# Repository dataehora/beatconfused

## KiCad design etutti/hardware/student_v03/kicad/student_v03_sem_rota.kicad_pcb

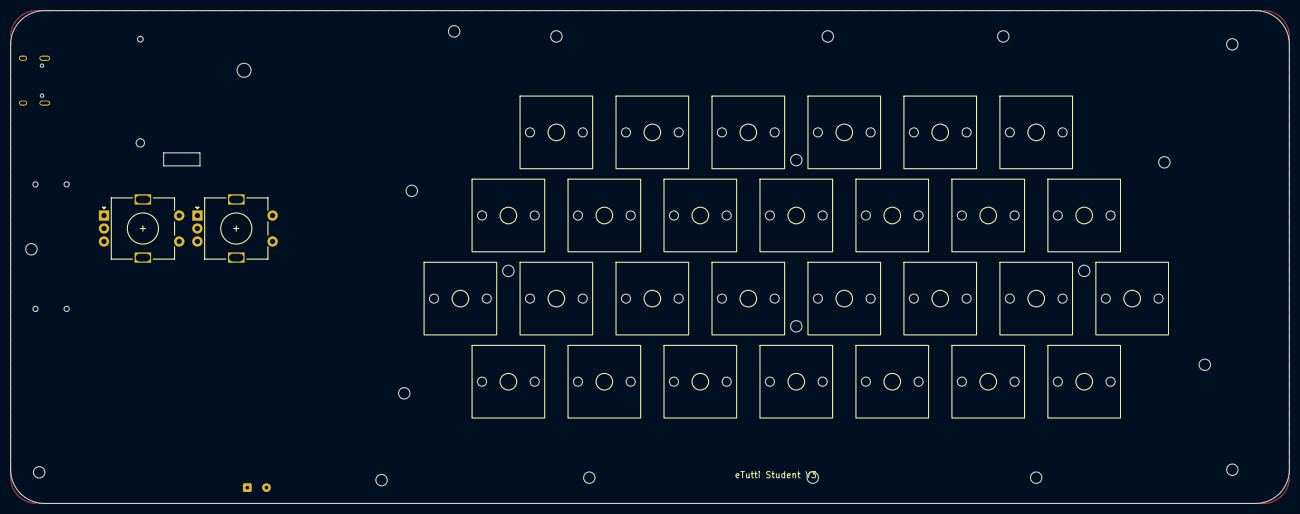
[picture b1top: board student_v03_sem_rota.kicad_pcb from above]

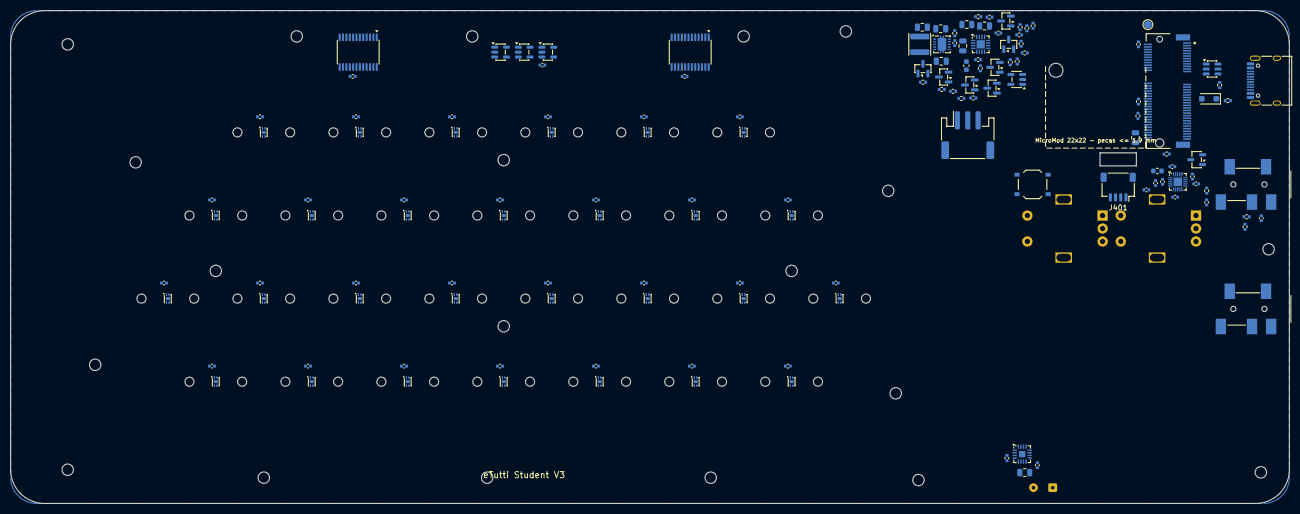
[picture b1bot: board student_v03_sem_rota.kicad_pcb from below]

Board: 4 copper layers, 246.5 x 95.0 mm, 190 parts (138 on the bottom side), 98 nets, no tracks yet.

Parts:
C101, C201, C202, C203, C206, C207, C208, C501: 10uF; C_0805_2012Metric
C102, C204, C205, C209, C302, C304, C305, C307, C308, C502, C601, C602, C603, C701, C702, C703, C704, C705, C706, C707, C708, C709, C710, C711, C712, C713, C714, C715, C716, C717, C718, C719, C720, C721, C722, C723, C724, C725, C726, C727, C728: 100nF; C_0402_1005Metric
C210: 10uF; C_0603_1608Metric
C213, C309: 1uF; C_0402_1005Metric
C301, C303, C306: 2.2uF; C_0402_1005Metric
D201: SMF5.0A; D_SOD-123F
D202, D203, D204, D205: BAV70; SOT-23
FB301: 600R@100MHz; L_0603_1608Metric
H1, H2, H3, H4, H5, H6, H7, H8, H9, H10: MountingHole_2.2mm_M2
H101: MountingHole_2.7mm_M2.5
HG1, HG2, HG3, HG4, HG5, HG6, HG7, HG8, HG9, HG10: MountingHole_2.2mm_M2
J101: 91302-42-067RCE; M.2_E_H4.2_UMAX_91302-42-067
J201: TYPE-C-31-M-12; USB_C_Receptacle_HRO_TYPE-C-31-M-12
J202: S3B-PH-SM4-TB; JST_PH_S3B-PH-SM4-TB_1x03-1MP_P2.00mm_Horizontal
J301, J302: PJ-327A 5JJ; Jack_3.5mm_PJ-327A_SMD
J401: SM04B-SRSS-TB; JST_SH_SM04B-SRSS-TB_1x04-1MP_P1.00mm_Horizontal
J501: alto-falante (fios); SolderWire-0.127sqmm_1x02_P3.7mm_D0.48mm_OD1mm
L201: 2.2uH; L_Changjiang_FNR4020S
Q201, Q203: AO3401A; SOT-23
Q202: AO3400A; SOT-23
R105, R216: 100; R_0402_1005Metric
R201, R202: 5.1k; R_0402_1005Metric
R203, R301, R302, R305: 2.2k; R_0402_1005Metric
R204: 1.5k; R_0402_1005Metric
R205, R214: 10k; R_0402_1005Metric
R206, R210, R211, R213, R215, R218, R303: 100k; R_0402_1005Metric
R207, R217: 1k; R_0402_1005Metric
R208, R209, R212, R304, R501: 1M; R_0402_1005Metric
SW1, SW2, SW3, SW4, SW5, SW6, SW7, SW8, SW9, SW10, SW11, SW12, SW13, SW14, SW15, SW16, SW17, SW18, SW19, SW20, SW21, SW22, SW23, SW24, SW25, SW26, SW27, SW28: Gateron_Magnetic_MX_1u
SW401, SW402: EC11E18244AU; RotaryEncoder_Alps_EC11E-Switch_Vertical_H20mm
SW403: Program; SW_Push_1P1T_XKB_TS-1187A
TP101: RESET#/ONOFF; TestPoint_Pad_D1.5mm
U201: USBLC6-2SC6; SOT-23-6
U202: BQ24074RGTR; VQFN-16-1EP_3x3mm_P0.5mm_EP1.6x1.6mm
U203, U604, U605: 74LVC1G08; SOT-23-5
U204: TPS63001DRCR; Texas_DRC0010J
U301: SGTL5000XNLA3; QFN-20-1EP_3x3mm_P0.4mm_EP1.65x1.65mm
U302: XC6206P182MR; SOT-23-3
U501: MAX98357AETE+T; TQFN-16-1EP_3x3mm_P0.5mm_EP1.23x1.23mm
U601, U602: 74HC4067PW; TSSOP-24_4.4x7.8mm_P0.65mm
U603: 74LVC1G04; SOT-23-5
U701, U702, U703, U704, U705, U706, U707, U708, U709, U710, U711, U712, U713, U714, U715, U716, U717, U718, U719, U720, U721, U722, U723, U724, U725, U726, U727, U728: TMAG5253BA3IQDMRR; Texas_X2SON-4-1EP_1.1x1.4mm_P0.5mm_EP0.8x0.6mm

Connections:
+3V3: C101.1, C102.1, C205.1, C207.1, C208.1, C303.1, C304.1, C305.1, C601.1, C602.1, C603.1, C701.1, C702.1, C703.1, C704.1, C705.1, C706.1, C707.1, C708.1, C709.1, C710.1, C711.1, C712.1, C713.1, C714.1, C715.1, C716.1, C717.1, C718.1, C719.1, C720.1, C721.1, C722.1, C723.1, C724.1, C725.1, C726.1, C727.1, C728.1, FB301.1, J101.2, J101.74, J401.2, Q202.1, R218.1, R301.1, R302.1, U203.5, U204.1, U204.10, U301.12, U302.3, U601.24, U602.24, U603.5, U604.5, U605.5, U701.1, U702.1, U703.1, U704.1, U705.1, U706.1, U707.1, U708.1, U709.1, U710.1, U711.1, U712.1, U713.1, U714.1, U715.1, U716.1, U717.1, U718.1, U719.1, U720.1, U721.1, U722.1, U723.1, U724.1, U725.1, U726.1, U727.1, U728.1
AMP_SD: J101.61, R501.1
AMP_SDM: R501.2, U501.4
AUD_MCLK: R105.2, U301.13
AUD_MCLK_P: J101.58, R105.1
BAT_NTC: J202.2, U202.1
BB_L1: L201.1, U204.4
BB_L2: L201.2, U204.2
BB_VINA: C209.1, R216.2, U204.8
CC1: J201.A5, R201.1
CC2: J201.B5, R202.1
CHGA: Q202.3, R207.2
CHGLED: Q201.3, R207.1
CHG_EN1: R205.2, U202.6
CHG_ILIM: R204.1, U202.12
CHG_ISET: R203.1, U202.16
CHG_N: D202.3, Q201.1, R206.2, U202.9
CHG_STAT: D202.1, J101.67
EN_A: U604.4, U701.3, U702.3, U703.3, U704.3, U705.3, U706.3, U707.3, U716.3, U717.3, U718.3, U719.3, U720.3, U721.3, U722.3
EN_B: U605.4, U708.3, U709.3, U710.3, U711.3, U712.3, U713.3, U714.3, U715.3, U723.3, U724.3, U725.3, U726.3, U727.3, U728.3
EN_REQ: D203.3, D204.3, R212.1, U204.6
GND: C101.2, C102.2, C201.2, C202.2, C203.2, C204.2, C205.2, C206.2, C207.2, C208.2, C209.2, C210.2, C213.2, C301.2, C302.2, C303.2, C304.2, C305.2, C306.2, C307.2, C308.2, C501.2, C502.2, C601.2, C602.2, C603.2, C701.2, C702.2, C703.2, C704.2, C705.2, C706.2, C707.2, C708.2, C709.2, C710.2, C711.2, C712.2, C713.2, C714.2, C715.2, C716.2, C717.2, C718.2, C719.2, C720.2, C721.2, C722.2, C723.2, C724.2, C725.2, C726.2, C727.2, C728.2, D201.2, J101.1, J101.7, J101.33, J101.36, J101.39, J101.45, J101.75, J101.MP, J201.A1, J201.A12, J201.B1, J201.B12, J201.SH, J202.3, J202.MP, J302.1, J302.2, J401.1, J401.MP, Q202.2, R201.2, R202.2, R203.2, R204.2, R209.2, R211.2, R212.2, R213.2, R215.2, R304.2, SW401.C, SW401.MP, SW401.S1, SW402.C, SW402.MP, SW402.S1, SW403.2, U201.2, U202.4, U202.5, U202.8, U202.17, U203.3, U204.3, U204.7, U204.9, U204.11, U301.21, U302.1, U501.3, U501.11, U501.15, U501.17, U601.12, U601.15, U602.12, U602.15, U603.3, U604.3, U605.3, U701.2, U701.5, U702.2, U702.5, U703.2, U703.5, U704.2, U704.5, U705.2, U705.5, U706.2, U706.5, U707.2, U707.5, U708.2, U708.5, U709.2, U709.5, U710.2, U710.5, U711.2, U711.5, U712.2, U712.5, U713.2, U713.5, U714.2, U714.5, U715.2, U715.5, U716.2, U716.5, U717.2, U717.5, U718.2, U718.5, U719.2, U719.5, U720.2, U720.5, U721.2, U721.5, U722.2, U722.5, U723.2, U723.5, U724.2, U724.5, U725.2, U725.5, U726.2, U726.5, U727.2, U727.5, U728.2, U728.5
HP_DET: C308.1, J101.22, R303.2, R304.1
HP_L: J301.4, U301.4
HP_R: J301.3, U301.1
HP_TIPSW: J301.5, R303.1
HP_VGND: J301.1, J301.2, U301.2
I2C_SCL: J101.14, J401.4, R302.2, U301.19
I2C_SDA: J101.12, J401.3, R301.2, U301.18
I2S_BCLK: J101.50, U301.15, U501.16
I2S_LRCLK: J101.52, U301.14, U501.14
I2S_RX: J101.54, U301.16
I2S_TX: J101.56, U301.17, U501.1
KEEP: D203.2, J101.55, R213.1
MIC_BIAS: R305.1, U301.11
MIC_IN: C309.2, U301.10
MIC_J: C309.1, J302.4, R305.2
MUX_L_COM: J101.38, U601.1
MUX_R_COM: J101.34, U602.1
MUX_S0: J101.19, U601.10, U602.10
MUX_S1: J101.17, U601.11, U602.11
MUX_S2: J101.47, U601.14, U602.14
MUX_S3: J101.32, U601.13, U602.13, U603.2, U605.1
NS3: U603.4, U604.1
ONOFF: D205.2, J101.6, TP101.1
OUT_K01: U601.4, U701.4
OUT_K02: U601.5, U702.4
OUT_K03: U601.8, U703.4
OUT_K04: U601.6, U704.4
OUT_K05: U602.7, U705.4
OUT_K06: U602.8, U706.4
OUT_K07: U602.9, U707.4
OUT_K08: U601.22, U708.4
OUT_K09: U601.21, U709.4
OUT_K10: U601.16, U710.4
OUT_K11: U601.18, U711.4
OUT_K12: U602.18, U712.4
OUT_K13: U602.20, U713.4
OUT_K14: U602.17, U714.4
OUT_K15: U602.16, U715.4
OUT_K16: U601.7, U716.4
OUT_K17: U601.2, U717.4
OUT_K18: U601.3, U718.4
OUT_K19: U602.5, U719.4
OUT_K20: U602.3, U720.4
OUT_K21: U602.4, U721.4
OUT_K22: U602.6, U722.4
OUT_K23: U601.19, U723.4
OUT_K24: U601.20, U724.4
OUT_K25: U601.23, U725.4
OUT_K26: U602.22, U726.4
OUT_K27: U602.23, U727.4
OUT_K28: U602.21, U728.4
PROG: J101.11, SW403.1
PWR_EN: J101.4, R217.1
PWR_EN_S: C213.1, R217.2, R218.2, U203.2
PWR_KEY: D203.1, Q203.3, R211.1
SEL_A: J101.59, SW402.A
SEL_B: J101.69, SW402.B
SEL_SW: J101.71, SW402.S2
SENS_EN: J101.10, U604.2, U605.2
SGTL_VAG: C307.1, U301.5
SGTL_VDDA: C301.1, C302.1, FB301.2, U301.3
SGTL_VDDD: C306.1, U301.20, U302.2
SPK_N: J501.2, U501.10
SPK_P: J501.1, U501.9
USB_DN: J101.5, J201.A7, J201.B7, U201.3, U201.4
USB_DP: J101.3, J201.A6, J201.B6, U201.1, U201.6
USB_HOLD: D204.1, U203.4
VBAT: C203.1, J202.1, R208.1, U202.2, U202.3
VBAT_S: C204.1, J101.20, R208.2, R209.1
VBUS: C201.1, D201.1, J101.9, J201.A4, J201.A9, J201.B4, J201.B9, Q201.2, R205.1, R206.1, R214.1, U201.5, U202.13
VBUS_S: R214.2, R215.1, U203.1
VOL_A: J101.49, SW401.A
VOL_B: J101.53, SW401.B
VOL_SW: D205.1, J101.51
VOL_SW_N: D205.3, Q203.1, R210.2, SW401.S2
VSYS: C202.1, C206.1, C210.1, C501.1, C502.1, Q203.2, R210.1, R216.1, U202.10, U202.11, U204.5, U501.7, U501.8

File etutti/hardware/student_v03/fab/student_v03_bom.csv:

Comment,Designator,Footprint,LCSC Part #
100nF,"C102,C204,C205,C209,C302,C304,C305,C307,C308,C502,C601,C602,C603,C701,C702,C703,C704,C705,C706,C707,C708,C709,C710,C711,C712,C713,C714,C715,C716,C717,C718,C719,C720,C721,C722,C723,C724,C725,C726,C727,C728",C_0402_1005Metric,C1525
2.2uF,"C301,C303,C306",C_0402_1005Metric,C12530
1uF,C309,C_0402_1005Metric,C52923
10uF,C210,C_0603_1608Metric,C19702
10uF,"C101,C201,C202,C203,C206,C207,C208,C501",C_0805_2012Metric,C15850
SMF5.0A,D201,D_SOD-123F,C151296
S3B-PH-SM4-TB,J202,JST_PH_S3B-PH-SM4-TB_1x03-1MP_P2.00mm_Horizontal,C265101
SM04B-SRSS-TB,J401,JST_SH_SM04B-SRSS-TB_1x04-1MP_P1.00mm_Horizontal,C160404
PJ-327A,"J301,J302",Jack_3.5mm_PJ-327A_SMD,C49284723
600R@100MHz,FB301,L_0603_1608Metric,C1002
2.2uH,L201,L_Changjiang_FNR4020S,C167825
91302-42-067RCE,J101,M.2_E_H4.2_UMAX_91302-42-067,C48985906
SGTL5000XNLA3,U301,QFN-20-1EP_3x3mm_P0.4mm_EP1.65x1.65mm,C2651833
100,"R105,R216",R_0402_1005Metric,C25076
5.1k,"R201,R202",R_0402_1005Metric,C25905
2.2k,"R203,R301,R302,R305",R_0402_1005Metric,C25879
1.5k,R204,R_0402_1005Metric,C25867
10k,"R205,R214",R_0402_1005Metric,C25744
100k,"R206,R210,R211,R213,R215,R303",R_0402_1005Metric,C25741
1M,"R208,R209,R212,R304,R501",R_0402_1005Metric,C26083
BAV70,"D202,D203,D205,D206",SOT-23,C68978
AO3401A,Q203,SOT-23,C15127
XC6206P182MR,U302,SOT-23-3,C347373
74LVC1G04,U603,SOT-23-5,C7827
74LVC1G08,"U604,U605",SOT-23-5,C7666
USBLC6-2SC6,U201,SOT-23-6,C7519
Program,SW403,SW_Push_1P1T_XKB_TS-1187A,C318884
MAX98357AETE+T,U501,TQFN-16-1EP_3x3mm_P0.5mm_EP1.23x1.23mm,C910544
74HC4067PW,"U601,U602",TSSOP-24_4.4x7.8mm_P0.65mm,C179326
TPS63001DRCR,U204,Texas_DRC0010J,C28060
TMAG5253BA3IQDMRR,"U701,U702,U703,U704,U705,U706,U707,U708,U709,U710,U711,U712,U713,U714,U715,U716,U717,U718,U719,U720,U721,U722,U723,U724,U725,U726,U727,U728",Texas_X2SON-4-1EP_1.1x1.4mm_P0.5mm_EP0.8x0.6mm,C22401868
TYPE-C-31-M-12,J201,USB_C_Receptacle_HRO_TYPE-C-31-M-12,C165948
BQ24074RGTR,U202,VQFN-16-1EP_3x3mm_P0.5mm_EP1.6x1.6mm,C54313

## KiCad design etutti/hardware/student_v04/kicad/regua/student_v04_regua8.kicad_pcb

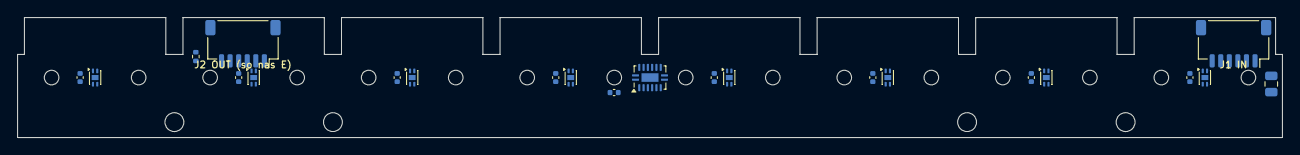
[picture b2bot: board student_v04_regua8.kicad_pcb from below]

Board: 4 copper layers, 147.6 x 14.0 mm, 42 parts (22 on the bottom side), 15 nets, no tracks yet.

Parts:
C1, C2, C3, C4, C5, C6, C7, C8, C9: 100nF; C_0402_1005Metric
C10: 10uF; C_0805_2012Metric
H1, H2, H3, H4: MountingHole_2.2mm_M2
J1, J2: SM06B-SRSS-TB(LF)(SN); JST_SH_SM06B-SRSS-TB_1x06-1MP_P1.00mm_Horizontal
PEG1a, PEG1b, PEG2a, PEG2b, PEG3a, PEG3b, PEG4a, PEG4b, PEG5a, PEG5b, PEG6a, PEG6b, PEG7a, PEG7b, PEG8a, PEG8b: MountingHole_2.2mm_M2
R1: 330; R_0402_1005Metric
U1, U2, U3, U4, U5, U6, U7, U8: TMAG5253BA3IQDMRR; Texas_X2SON-4-1EP_1.1x1.4mm_P0.5mm_EP0.8x0.6mm
U9: 74HC595BQ,115; DHVQFN-16-1EP_2.5x3.5mm_P0.5mm_EP1x2mm

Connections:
+3V3: C1.1, C2.1, C3.1, C4.1, C5.1, C6.1, C7.1, C8.1, C9.1, C10.1, J1.1, J2.1, U1.1, U2.1, U3.1, U4.1, U5.1, U6.1, U7.1, U8.1, U9.10, U9.16
CLK: J1.5, J2.5, U9.11, U9.12
EN1: U1.3, U9.15
EN2: U2.3, U9.1
EN3: U3.3, U9.2
EN4: U4.3, U9.3
EN5: U5.3, U9.4
EN6: U6.3, U9.5
EN7: U7.3, U9.6
EN8: U8.3, U9.7
GND: C1.2, C2.2, C3.2, C4.2, C5.2, C6.2, C7.2, C8.2, C9.2, C10.2, J1.2, J1.4, J1.MP, J2.2, J2.4, J2.MP, U1.2, U1.5, U2.2, U2.5, U3.2, U3.5, U4.2, U4.5, U5.2, U5.5, U6.2, U6.5, U7.2, U7.5, U8.2, U8.5, U9.8, U9.13, U9.17
OUT: J1.3, J2.3, U1.4, U2.4, U3.4, U4.4, U5.4, U6.4, U7.4, U8.4
QHP: R1.1, U9.9
QHP_J: J2.6, R1.2
SER: J1.6, U9.14
